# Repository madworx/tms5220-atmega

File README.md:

# TMS5220 Exploration unit

This project was created to try out the Texas Instruments TMS5220 _Voice synthesis processor_ (of TI99/4A, Apple II Echo 2, and various pinball/arcade games fame).

First off, a word of warning: The PCB being powered by potentially three sources (PSU, Communication USB, AVR ISP), I've observed some weird behavior with power unexpectedly flowing in the wrong direction, causing intermittent system interruptions, host USB-port lock-up requiring system restart and one burnt MCU.

Preferably disconnect the PSU before connecting the ISP and move the `J3` jumper to programming mode.

The project as it currently is is rather "build your own" but since the project was created to let me toy with the TMS5220 chip, it's not likely to see any major improvements in the forseeable future.

## Software environment

* `avrdude`
* `avr-gcc`

## Peripherials setup

### Programmer (AVR ISP)

I used a cheap `usbasp` clone.

### UB232R

The `UB232R` interface needs to be configured using the [FT_Prog] tool:

* `High Current I/O's` to be disabled.

* Under the `IO Controls` section, output on pin `C0` should be set to `CLK12`, providing the Atmega 328P with a system clock of 12MHz.

The baud rate is the USB interface is configured by the host operating system driver. The MCU UART baud rate need to be matched to this.

[FT_Prog]: https://www.ftdichip.com/Support/Utilities.htm#FT_PROG

### Atmega 328P

* `lfuse` should be programmed to _external clock without /8DIV_ (`0xE0`):

```
avrdude -p m328p -c usbasp -U lfuse:w:0xE0:m
```

## TMS5220 details

### D/A

10-bit twos-complement.

```
|           |  PC latice outputs                                      |            |             |
|-----------|---------------------------------------------------------|------------|-------------|
| Value     |  YD  YC  YB  YA  Y9  Y8  Y7  Y6  Y5  Y4  Y3  Y2  Y1  Y0 | D/A input  | Analog (uA) |
|-----------|---------------------------------------------------------|------------|-------------|
| > +127    |  0   1   1   x   x   x   x   x   x   x   x   x   x   x  |  11111111  |      0      |
| > +127    |  0   1   0   x   x   x   x   x   x   x   x   x   x   x  |  11111111  |      0      |
| > +127    |  0   0   1   x   x   x   x   x   x   x   x   x   x   x  |  11111111  |      0      |
| +127      |  0   0   0   1   1   1   1   1   1   1   1   x   x   x  |  11111111  |      0      |
| +126      |  0   0   0   1   1   1   1   1   1   1   0   x   x   x  |  11111110  |      5.86   |
| etc.      |  0   0   0   .   .   .   .   .   .   .   .   x   x   x  |  ........  |     .....   |
| +1        |  0   0   0   0   0   0   0   0   0   0   1   x   x   x  |  10000001  |    738.00   |
| 0         |  0   0   0   0   0   0   0   0   0   0   0   x   x   x  |  10000000  |    744.00   |
| -1 (off)  |  1   1   1   1   1   1   1   1   1   1   1   x   x   x  |  01111111  |    750.00   |
| -2        |  1   1   1   1   1   1   1   1   1   1   0   x   x   x  |  01111110  |    755.80   |
| etc.      |  1   1   1   .   .   .   .   .   .   .   .   x   x   x  |  ........  |   .......   |
| -128      |  1   1   1   0   0   0   0   0   0   0   0   x   x   x  |  00000000  |   1500.00   |
| < -128    |  1   1   0   x   x   x   x   x   x   x   x   x   x   x  |  00000000  |   1500.00   |
| < -128    |  1   0   1   x   x   x   x   x   x   x   x   x   x   x  |  00000000  |   1500.00   |
| < -128    |  1   0   0   x   x   x   x   x   x   x   x   x   x   x  |  00000000  |   1500.00   |
```

### Timing diagram

* `ROMCLK` = 160kHz (= 6,26uS = 75x 12MHz cycles -> 37.5 cycles per level):
* `T11` is pulled high before the start of each 10-bit word. (Note: The `T11`/`IO` cycle will run as long as the TMS chip is powered, regardless if any `SPEAK` or `SPEAK EXTERNAL` commands are currently running or not.)

```
 | 36| 36| 36| Clock cycles @ 12MHz

                             |
  ___     ___     ___     ___v    ___     ___     ___     ___     ___     ___     ___     ___     ___     
_|   |___|   |___|   |___|   |___|   |___|   |___|   |___|   |___|   |___|   |___|   |___|   |___|   |___|   *ROMCLK*
          _______            :
_________|       |___________:____________________________________________________________________________   *T11*
                          ___:___________________________________________________________________________
_________________________|  lsb  |       |       |       |       |       |       |       |       |  msb  |   *I/O*
                             ^
                             |
                             +-- This is where we sample & store the value of I/O.
```

## Code structure 

* TMS5220 flag us that it's ready to receive data with the use of the `~READY` signal.

* On negative edge trigger: Sample I/O pin, shift storage byte and add bit. (This should be in the range of ~15 instructions)

* On positive edge trigger: Perform state-based logic (max ~35 clock cycles to complete each operation).

* A full write of `DBUS` on the TMS requires us to write to three different ports on the Atmega. (~15 instructions each)

## Accessing the USB UART under linux with 250000 baud rate

```
 $ setserial -a /dev/ttyUSB0 spd_cust
 $ setserial -a /dev/ttyUSB0 divisor 64 # for 375000
 $ setserial -a /dev/ttyUSB0 divisor 96 # for 250000
 $ stty -F /dev/ttyUSB0 38400
 $ socat TCP-L:1147 FILE:/dev/ttyUSB0,b38400,raw,echo=0
```

## Afterthoughts on PCB design

* Atmega reset button on PCB would be nice.
* Proximity to other components makes the jumpers hard to access.
* Should have used a trimmer with lower resistance and a base resistor of higher value to enable more accurate tuning of `ROMCLK`.
* Possibly some form of "mode switch" to select different functions in the MCU.
* Could likely have been powered by USB directly, eliminating the external PSU. (However, need to take into account that +5 and -5V needs to be applied more or less simultaneous)
* Hard to dislodge the TMS chip due to resistor in the way.
* Bottom mounting of TMS resistor on PCB due to placement near socket edge -- has been fixed in current PCB layout, but not in manufactured ones.
* Hard to dislodge Atmega328P due to resistor in the way -- has been fixed in current PCB layout, but not in manufactured ones.
* A status LED or two would be nice.
* Reading more about the TMS chip, I could have driven the "TESTING USE ONLY" `PROMOUT` pin to -5 to enable external clocking, removing timing constraints for the MCU.
* The "programming mode" jumper in the end turned out quite useless -- a proper RESET of the TMS-chip usually cleared up any inconsistencies.
* Multiple pins connected to TMS5220 that in the end weren't needed.
* Power drainage is much higher than expected; Around 500mA and LM7805 reaches 51 degrees C.

## Oscillator caps

### TMS5220 T11, ROMCLK, IO

### TMS5220 ROMCLK output

### UB232R-CLK12

Connected to Atmega328P:

## References

* [TMS5220 Data sheet PDF](references/tms5220.pdf)
* [TMS5220 reference from www.unige.ch](http://www.unige.ch/medecine/nouspikel/ti99/speech.htm)

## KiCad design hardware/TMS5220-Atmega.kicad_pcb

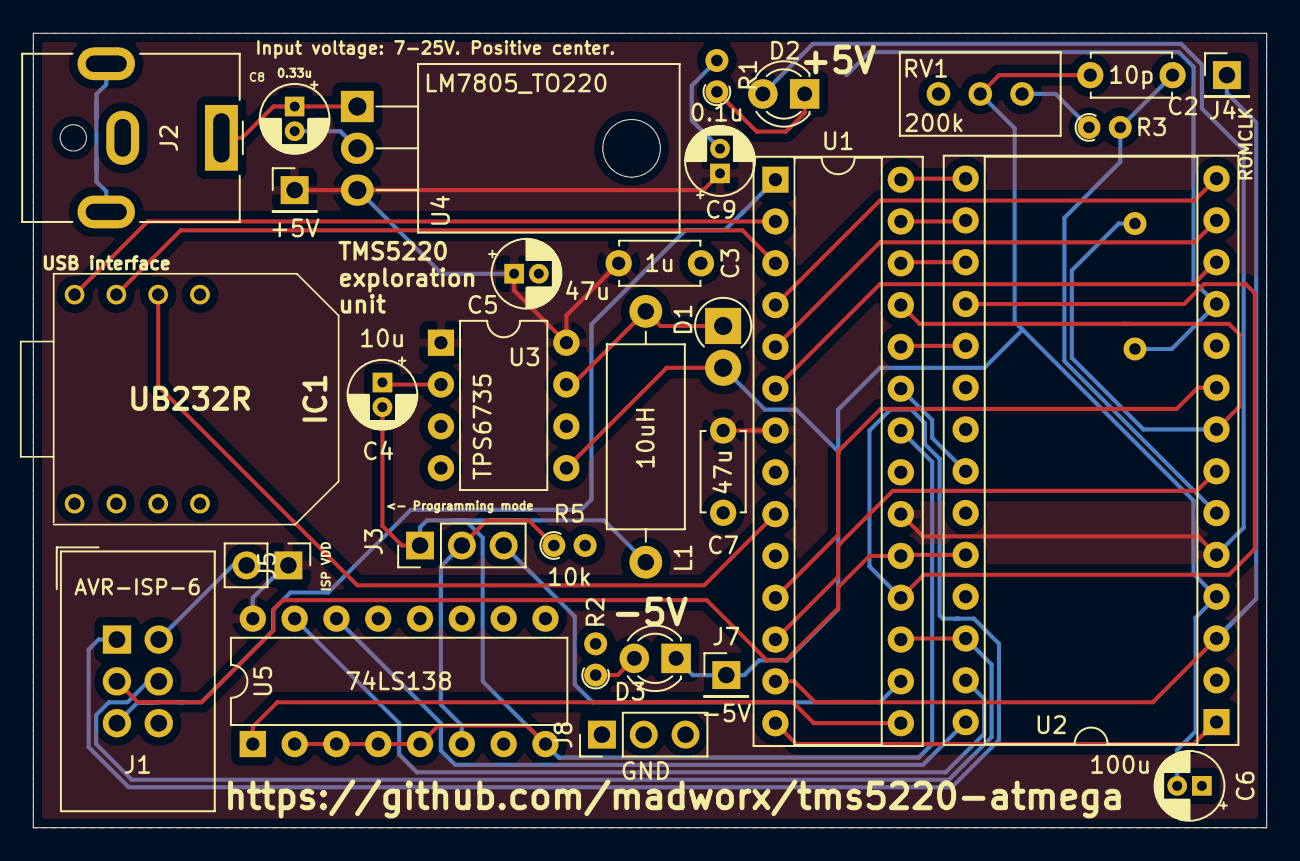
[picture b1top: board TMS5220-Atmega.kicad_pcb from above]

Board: 2 copper layers, 74.9 x 48.3 mm, 32 parts (1 on the bottom side), 36 nets.

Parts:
C2: 10p; C_Disc_D4.7mm_W2.5mm_P5.00mm
C3: 1u; C_Disc_D4.7mm_W2.5mm_P5.00mm
C4: 10u; CP_Radial_D4.0mm_P1.50mm
C5: 47u; CP_Radial_D4.0mm_P1.50mm
C6: 100u; CP_Radial_D4.0mm_P1.50mm
C7: 47u; C_Disc_D4.7mm_W2.5mm_P5.00mm
C8: 0.33u; CP_Radial_D4.0mm_P1.50mm
C9: 0.1u; CP_Radial_D4.0mm_P1.50mm
D1: D_Schottky; D_DO-41_SOD81_P2.54mm_Vertical_AnodeUp
D2, D3: LED; LED_D3.0mm
IC1: UB232R
J1: AVR-ISP-6; IDC-Header_2x03_P2.54mm_Vertical
J2: Barrel_Jack_MountingPin; BarrelJack_CUI_PJ-063AH_Horizontal
J3: Conn_01x03; PinHeader_1x03_P2.54mm_Vertical
J4: ROMCLK; PinHeader_1x01_P2.54mm_Vertical
J5: Conn_01x02; PinHeader_1x02_P2.54mm_Vertical
J6: +5V; PinHeader_1x01_P2.54mm_Vertical
J7: -5V; PinHeader_1x01_P2.54mm_Vertical
J8: GND; PinHeader_1x03_P2.54mm_Vertical
L1: 10uH; L_Axial_L11.0mm_D4.5mm_P15.24mm_Horizontal_Fastron_MECC
R1, R2: 220; R_Axial_DIN0204_L3.6mm_D1.6mm_P1.90mm_Vertical
R3: 47k; R_Axial_DIN0204_L3.6mm_D1.6mm_P1.90mm_Vertical
R4: 3k3; R_Axial_DIN0204_L3.6mm_D1.6mm_P7.62mm_Horizontal
R5: 10k; R_Axial_DIN0204_L3.6mm_D1.6mm_P1.90mm_Vertical
RV1: 200k; Potentiometer_Bourns_3296W_Vertical
U1: ATmega328P-PU; DIP-28_W7.62mm_Socket
U2: TMS5220; DIP-28_W15.24mm_Socket
U3: TPS6735; DIP-8_W7.62mm
U4: LM7805_TO220; TO-220-3_Horizontal_TabDown
U5: 74LS138; DIP-16_W7.62mm

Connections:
+5V: C3.1, C5.1, C7.1, C9.1, D2.2, J5.1, J6.1, U1.7, U1.20, U2.5, U3.1, U3.8, U4.3, U5.16
-5V: C2.2, C6.2, D1.2, D3.1, J7.1, RV1.2, U2.4, U3.5
/ADCIN: R4.1, U1.25, U2.8
/DBUS0: U1.4, U2.14
/DBUS1: U1.5, U2.13
/DBUS2: U1.6, U2.12
/DBUS3: U1.24, U2.19
/DBUS4: U1.23, U2.22
/DBUS5: J1.3, U1.19, U2.24
/DBUS6: J1.4, U1.17, U2.26
/DBUS7: U1.14, U2.1
/IO: U1.11, U2.9
/ISPVDD: J1.2, J5.2
/M0: U1.28, U2.15
/M1: U1.27, U2.16
/OSC: C2.1, R3.2, U2.6
/REF: C4.1, U3.2
/ROMCLK: J4.1, U1.13, U2.3
/RW: U1.15, U5.1
/RW_EN: J3.3, U1.16
/SYSCLK: IC1.6, U1.9
/T11: U1.12, U2.7
/UART_RX: IC1.8, U1.2
/UART_TX: IC1.7, U1.3
/VIN: C8.1, J2.1, U4.1
/~INT: U1.26, U2.17
/~READY: J1.1, U1.18, U2.18
/~RESET: J1.5, U1.1
/~RS: U2.28, U5.14
/~WS: U2.27, U5.15
GND: C3.2, C4.2, C5.2, C6.1, C7.2, C8.2, C9.2, IC1.1, J1.6, J2.2, J3.1, J8.1, J8.2, J8.3, L1.2, R1.2, R2.2, R4.2, R5.2, U1.8, U1.22, U2.11, U3.6, U4.2, U5.2, U5.3, U5.4, U5.5, U5.8
unnamed: D1.1, L1.1, U3.7
unnamed: D2.1, R1.1
unnamed: D3.2, R2.1
unnamed: J3.2, R5.1, U5.6
unnamed: R3.1, RV1.1

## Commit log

2020-04-24 Initial import.
